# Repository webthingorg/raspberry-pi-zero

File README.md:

📸 Raspberry Pi Zero Hardware

## Pictures

## Schematic

[PDF](raspberry-pi-zero.pdf)

## Bill Of Materials

[Interactive BOM](https://gitlab.com/webthing.org/raspberry-pi-zero/-/raw/main/raspberry-pi-zero-bom.html?inline=false)

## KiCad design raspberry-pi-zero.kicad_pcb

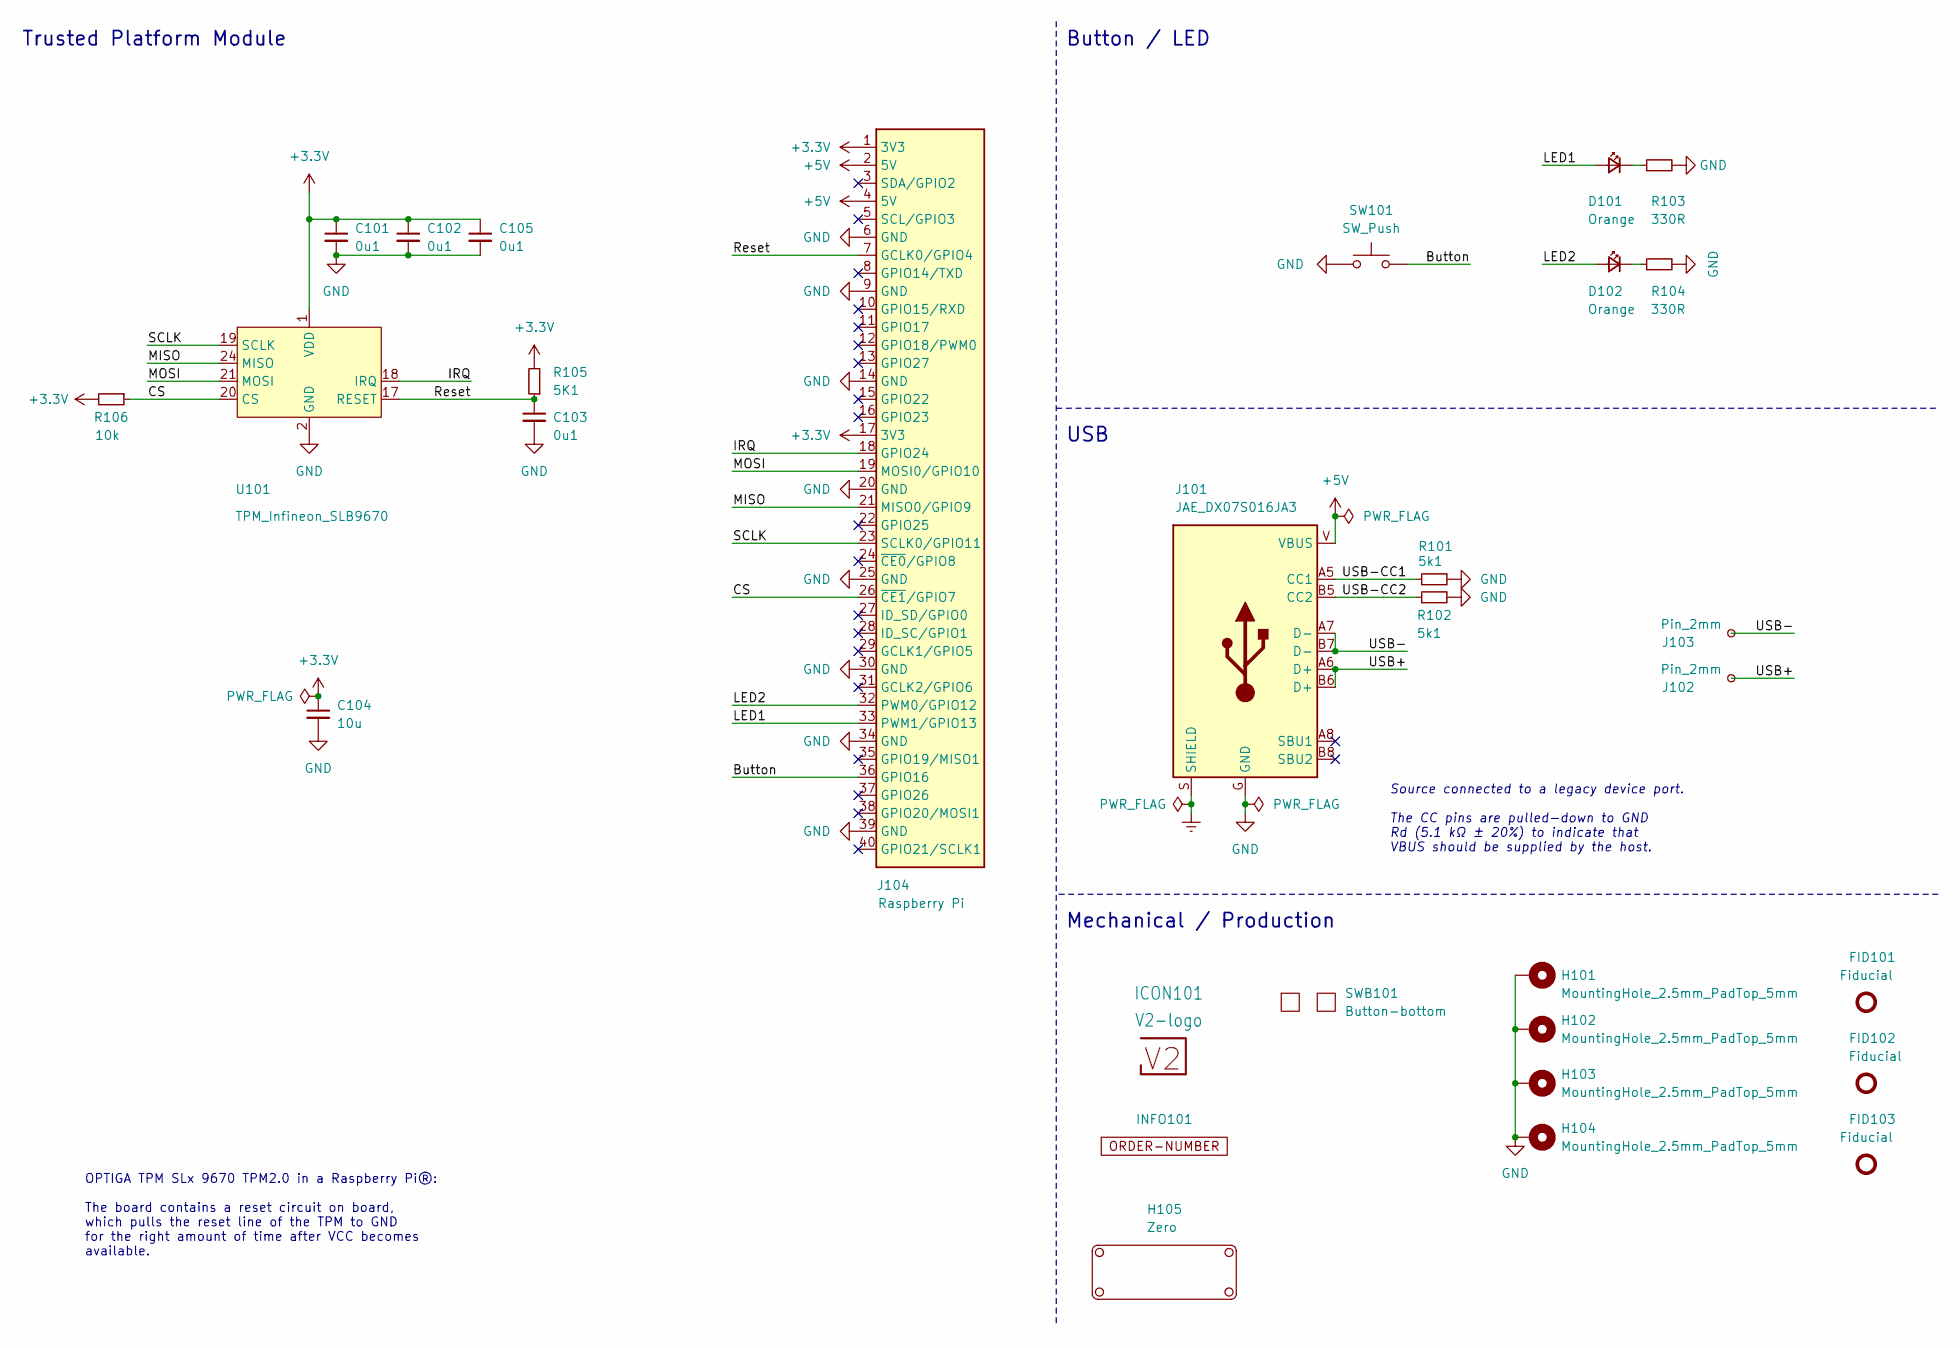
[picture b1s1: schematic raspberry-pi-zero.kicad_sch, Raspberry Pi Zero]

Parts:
C101, C102, C103, C105: 0u1; C_0603_1608Metric
C104: 10u; C_0603_1608Metric
D101, D102: Orange; LED_0603_1608Metric
FID101, FID102, FID103: Fiducial; Fiducial_0.5mm_Mask1mm_Paste
H101, H102, H103, H104: MountingHole_2.5mm_PadTop_5mm
H105: Zero
ICON101: V2-logo; Logo_Small
INFO101: ORDER-NUMBER; Order_Number
J101: JAE_DX07S016JA3
J102, J103: Pin_2mm
J104: Raspberry Pi; Connector_PogoPins
R101, R102: 5k1; R_0603_1608Metric
R103, R104: 330R; R_0603_1608Metric
R105: 5K1; R_0603_1608Metric
R106: 10k; R_0603_1608Metric
SW101: SW_Push; SKSG
SWB101: Button-bottom; PCB_Button-bottom
U101: TPM_Infineon_SLB9670; QFN-32-1EP_5x5mm_P0.5mm_EP3.6x3.6mm_ThermalVias

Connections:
+3.3V: C101.1, C102.1, C104.1, C105.1, J104.1 (3V3), J104.17 (3V3), R105.2, R106.2, U101.1 (VDD), U101.8 (VDD), U101.14 (VDD), U101.22 (VDD)
+5V: J101.V (VBUS), J104.2 (5V), J104.4 (5V)
/Button: J104.36 (GPIO16), SW101.2
/CS: J104.26 (~CE1/GPIO7), R106.1, U101.20 (CS)
/IRQ: J104.18 (GPIO24), U101.18 (IRQ)
/LED1: D101.2 (A), J104.33 (PWM1/GPIO13)
/LED2: D102.2 (A), J104.32 (PWM0/GPIO12)
/MISO: J104.21 (MISO0/GPIO9), U101.24 (MISO)
/MOSI: J104.19 (MOSI0/GPIO10), U101.21 (MOSI)
/Reset: C103.1, J104.7 (GCLK0/GPIO4), R105.1, U101.17 (RESET)
/SCLK: J104.23 (SCLK0/GPIO11), U101.19 (SCLK)
/USB+: J101.A6 (D+), J101.B6 (D+), J102.1
/USB-: J101.A7 (D-), J101.B7 (D-), J103.1
/USB-CC1: J101.A5 (CC1), R101.1
/USB-CC2: J101.B5 (CC2), R102.1
Earth: J101.S (SHIELD)
GND: C101.2, C102.2, C103.2, C104.2, C105.2, H101.1, H102.1, H103.1, H104.1, J101.G (GND), J104.6 (GND), J104.9 (GND), J104.14 (GND), J104.20 (GND), J104.25 (GND), J104.30 (GND), J104.34 (GND), J104.39 (GND), R101.2, R102.2, R103.2, R104.2, SW101.1, U101.2 (GND), U101.9 (GND), U101.16 (GND), U101.23 (GND), U101.32 (GND), U101.33 (GND)
unnamed: D101.1 (K), R103.1
unnamed: D102.1 (K), R104.1

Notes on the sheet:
Button / LED
Trusted Platform Module
﻿Source connected to a legacy device port. The CC pins are pulled-down to GND Rd (5.1 kΩ ± 20%) to indicate that VBUS should be supplied by the host.
Mechanical / Production
OPTIGA TPM SLx 9670 TPM2.0 in a Raspberry Pi®: The board contains a reset circuit on board, which pulls the reset line of the TPM to GND for the right amount of time after VCC becomes available.
USB

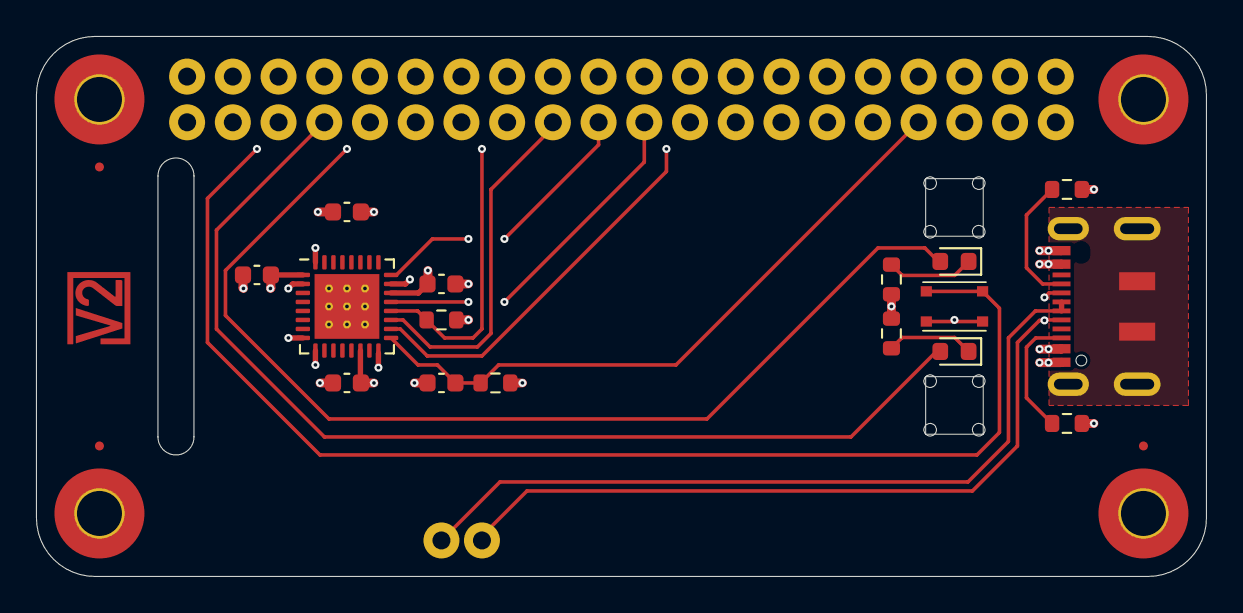
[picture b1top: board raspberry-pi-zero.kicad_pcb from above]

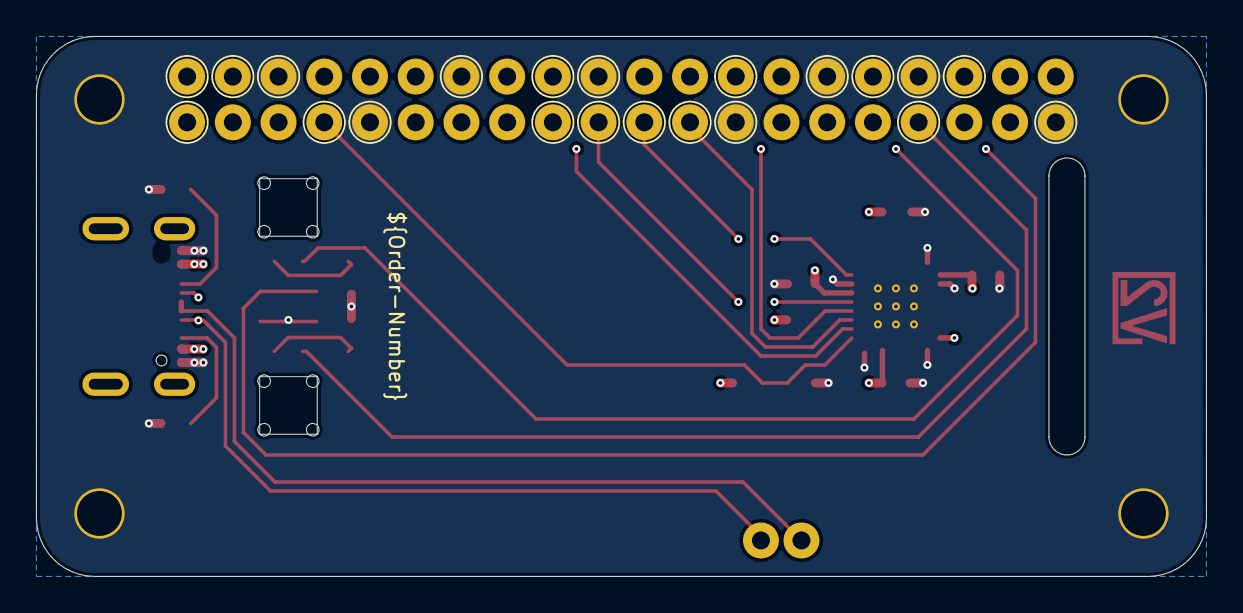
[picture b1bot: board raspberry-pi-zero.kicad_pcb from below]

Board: 4 copper layers, 65.0 x 30.0 mm, 30 parts (2 on the bottom side), 18 nets.

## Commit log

2024-09-26 Import
